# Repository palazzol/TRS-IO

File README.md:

# TRS-IO

TRS-IO gives a TRS-80 Model 1/III online capabilities and provides
access to a variety of services. TRS-IO currently features the
following capabilities:

1. Access to the <a href="https://retrostore.org">RetroStore</a>
2. <a href="http://frehd.com">FreHD</a> emulation
3. Access to files mounted on a SMB share or located on a micro-SD card
4. Access to remote servers via TCP
5. Virtual printer support

The TRS-IO versions for the Model 1 have some additional features that
are explained below. The following sections give an overview of TRS-IO as well as setup
instructions. This Github repository contains the complete source code
as well as the KiCad schematics for the PCB (Printed Circuit Board).
For the following descriptions it is assumed that an assembled TRS-IO
card is available.

### Overview

The figure below depicts the overall architecture. The TRS-80 machine
is connected to TRS-IO via the I/O Bus.  TRS-IO has a WiFi module that
connects to the local WiFi router. This allows TRS-IO to connect to
the Internet and access various services. Note that TRS-IO can only
connect to a 2.4 GHz WiFi network.

### Prerequisites

TRS-IO requires a TRS-80 Model III with 48kB of RAM or a Model 1 with 16kB of RAM.
Floppy disk drives or a cassette tape are not required.

### Feature list

TRS-IO support
TRS-IO comes in three different versions:

* TRS-IO for the Model III
* TRS-IO for the Model I using a builtin 32kB SRAM
* TRS-IO for the Model I using an FPGA

In the following, each of the versions is explained in detail.

### TRS-IO for the Model III

The following figure shows the top view of the TRS-IO card for the Model III:

1. Power supply via a micro-USB connector
2. Multi-color status LED
3. Status button
4. TRS-80 I/O bus connector
5. Micro-SD card reader
6. Disable FreHD jumper

The TRS-IO card needs to be connected to the TRS-80 Model III's I/O
Bus via a 50-pin ribbon cable (4). Furthermore, the TRS-IO card needs
a separate power supply via a standard 5V USB charger. The micro-USB
connector (1) plugs into the side of the TRS-IO card. The push button
(3) and the multi-color status LED (2) will be explained in the
configuration section.

### TRS-IO for the Model 1 (SRAM edition)

The following figure shows the top view of the TRS-IO card for the Model 1:

1. Power supply via a micro-USB connector
2. Multi-color status LED
3. Status button
4. TRS-80 I/O bus connector
5. Micro-SD card reader

The TRS-IO version for the Model 1 is almost identical to the Model III.
One difference is the I/O bus connector (4) is compatible with the 40-pin
expansion interface of the Model 1. There are several additional features
for the Model 1 version that are not relevant to the Model III version:

* A 32kB SRAM chip for a total of 48kB of total RAM.
* 25ms heartbeat timer to trigger the realtime clock.
* FreHD auto-boot for an unmodified M1.

### TRS-IO for the Model 1 (FPGA edition)

The TRS-IO project features a second version for the Model 1 that makes use
of an FGPA (Field Programmable Gate Array). Using an FPGA allows for some
advanced features not possible with the SRAM edition of TRS-IO. The following
figure shows the top view of the FPGA version for the Model 1:

1. Power supply via a micro-USB connector
2. Multi-color status LED
3. Status button
4. TRS-80 I/O bus connector
5. Micro-SD card reader
6. N/A
7. VGA connector
8. A15/VU configuration jumpers

This version of TRS-IO offers all the features of the SRAM edition of TRS-IO
as outlined in the previous section. Additionally, the FPGA edition also
offers a VGA connector (7) that can be used instead of a CRT monitor. This version
of TRS-IO also emlates the LE18 graphics cards. The color of the VGA signal can
be set to white (X=0), green (X=1), and amber (X=2) via the following OUT statements:

```OUT 31,0:OUT 31,5:OUT 31,X```

There are two configuation jumpers (8):
With the VU jumper, the ESP also powers the FPGA. When using this jumper, the FPGA
SHOULD NOT be powered via its own micro-USB connector; power should only be supplied
to the ESP's micro-USB connector (1). The A15 jumper regulates
the address range the FPGA responds to. Without the A15 jumper, the FPGA only
responds to memory read/write requests for the upper 32 kB (essentially mimicking the
upper RAM of the SRAM edition). With the A15 jumper, the FPGA will respond to the
complete 64kB address space of the Z80. This requires a modified Model 1 as the FPGA also
responds to ROM read requests.

### Configuring TRS-IO

The core of the TRS-IO card is an ESP32 microcontroller that features
a WiFi module that is used to connect to a WiFi router. After
physically connecting the TRS-IO card to a TRS-80 Model 1/III as
explained in the previous sections, the WiFi module on the ESP32
microcontroller first needs to be be configured with the credentials
of the local WiFi network.

While in setup mode, the TRS-IO's status LED will continuously blink
in white to indicate that it has not yet been configured. While in
that mode, TRS-IO will create an open access point called
"TRS-IO". Use a laptop to connect to this WiFi network and then use a
browser to visit URL <a
href="http://trs-io.local">trs-io.local</a>. The following web page
should appear in the browser:

Some hosts do not correctly handle mDNS that is used to resolve <a
href="http://trs-io.local">trs-io.local</a>. In that case, visit the
IP address <a href="http://192.168.4.1">192.168.4.1</a> instead.
The web interface shown above can be used to configure SSID and password of the WiFi
network that TRS-IO should connect to, the local timezone as well as
the credentials of a SMB share. For open networks leave the WiFi
password field empty. Note that TRS-IO cannot connect to WiFi networks
that use a capture portal. The timezone as well as the SMB share are
not required but will result in limited functionality.

Once all the information is provided, click on submit to upload the
parameters. TRS-IO will automatically reboot and try to connect to the
specified WiFi network. If successful, the LED will turn green for a
few seconds. If the credentials are wrong or if the specified WiFi
network is not accessible, the LED light will turn permanently red.

Note that TRS-IO will store all parameters in its local flash memory,
so the setup only needs to be performed once. Once TRS-IO is connected
to a WiFi router, it should still be possible to access URL <a
href="http://trs-io.local">trs-io.local</a> from a browser on the same
WiFi network. If mDNS is not supported by the host, the following BASIC
program can be used to determine TRS-IO's local IP address that was
assigned by the router:

```
10 OUT 236,16
20 OUT31,0:OUT31,4
30 C=INP(31):IF C=0 THEN END
40 PRINT CHR$(C);
50 GOTO 30
```

The web interface will also display two icons to indicate the status
of the SMB share and the micro-SD card (see screenshot above). Green
icons indicate that TRS-IO has access. Red icons indicate an error.
In that case, hovering the mouse over the red icon will display the
error message. It should be noted that TRS-IO needs to be rebooted
whenever a micro-SD card is inserted or ejected.

Pushing the status button will make the LED flash twice. The first time for
the WiFi status (green: WiFi connected; red: WiFi not connected) and a
second time for the SMB status (green: connected to SMB share; red:
not connected to SMB share). With proper configuration parameters, the
LED should flash green twice. Holding down the push button for more
than three seconds will erase all configuration parameters and place
TRS-IO back into setup mode (status LED flashing white). This
might be necessary if TRS-IO is moved to a different WiFi network.

The status LED indicates the state of TRS-IO:

* Blinking white: TRS-IO is not configured. It will create an open WiFi access point named "TRS-IO"
* Solid green: when TRS-IO has been configured with WiFi credentials and TRS-IO was able
  to connect to the WiFi network, the status LED will light in solid green for several seconds.
* Solid red: TRS-IO was configured with WiFi credentials but it was not possible to connect to the specified
  network. The reason could be wrong credentials or the specified network is itself offline. The push button can be
  used to reset TRS-IO into setup mode in case different credentials need to be provided.
* Solid blue: TRS-IO performs an OTA (Over-the-Air) update. TRS-IO will automatically detect
  newer firmware versions and will download and install the new firmware. The status LED will light solid blue during
  this process.
* Off: the status LED will be off during regular operations when TRS-IO is connected to the specified
  WiFi network and ready to accept commands from the TRS-80 Model III.
 
### FreHD

TRS-IO is compatible with the popular <a
href="http://frehd.com">FreHD</a> hard disk emulator. The FreHD disk
images can either be stored on a SMB share or on a micro-SD card.
If a micro-SD card is inserted, it will take precedence over
a mounted SMB share. Once TRS-IO is configured to access a SMB share,
simply copy the required files such as <a
href="http://members.iinet.net.au/~ianmav/trs80/downloads.htm">FREHD.ROM</a>
to the SMB share. Alternatively, the disk images can be transferred
to the micro-SD card. The IMPORT/EXPORT utilities will access files on the
SMB share or micro-SD card respectively.

### Virtual Printer Interface

TRS-IO support a virtual printer interface. Visiting <a
href="http://trs-io.local/printer">trs-io.local/printer</a> from a browser
will open the printer interface. Any printer output from the M1/MIII will
be displayed in the printer interface. If the host cannot resolve the mDNS name
trs-io.local, the above BASIC program can be used to determine the TRS-80's
IP address.

 ### Launching the native RetroStore Client

The <a href="https://retrostore.org">RetroStore</a> hosts applications
for the Tandy Radio Shack vintage computers and allows to seamlessly
download and run these applications without the need of cassettes or
floppy disks. TRS-IO acts as a gateway to the <a
href="https://retrostore.org">RetroStore</a>. This requires to run a
program on the TRS-80 that interfaces with TRS-IO. This program is
available as a regular <a
href="https://github.com/apuder/TRS-IO/blob/master/src/esp/components/retrostore/rsclient.cmd">CMD</a>
executable.  For TRS-80 machines with attached physical floppy disks,
this CMD executable can be copied to a floppy disk and launched the
usual way. For TRS-80 machines that have neither floppy disk drives
nor cassette drives, it is also possible to bootstrap the native
client via the following short BASIC program:
 
 ```BASIC
 10 OUT236,16
 20 OUT31,3
 30 OUT31,1
 40 N=INP(31)+256*INP(31)
 50 FOR X=1 TO N:POKE20735+X,INP(31):NEXT
 RUN
 SYSTEM
 *? /20736
 ```
 
The above BASIC program will download the CMD executable from TRS-IO
and launch the native client.  Note that this procedure needs to be
repeated every time the TRS-80 is turned on.
 
### Using the native RetroStore Client

After successfully launching the native RetroStore client, the monitor
of the TRS-80 should look like this:

The screenshot above shows the main menu of the native RetroStore
client. The arrow indicates the currently selected menu item.  The up
and down cursor keys can be used to move between the various menu
items. Hitting the ENTER key will activate the currently selected
menu item. Pressing CLEAR or BREAK in sub-menus will return to the
previous menu.
 
Keyboard controls:
 
 * Cursor up/down: toggle menu selection
 * ENTER: select current menu selection
 * BREAK/CLEAR: exit to previous screen

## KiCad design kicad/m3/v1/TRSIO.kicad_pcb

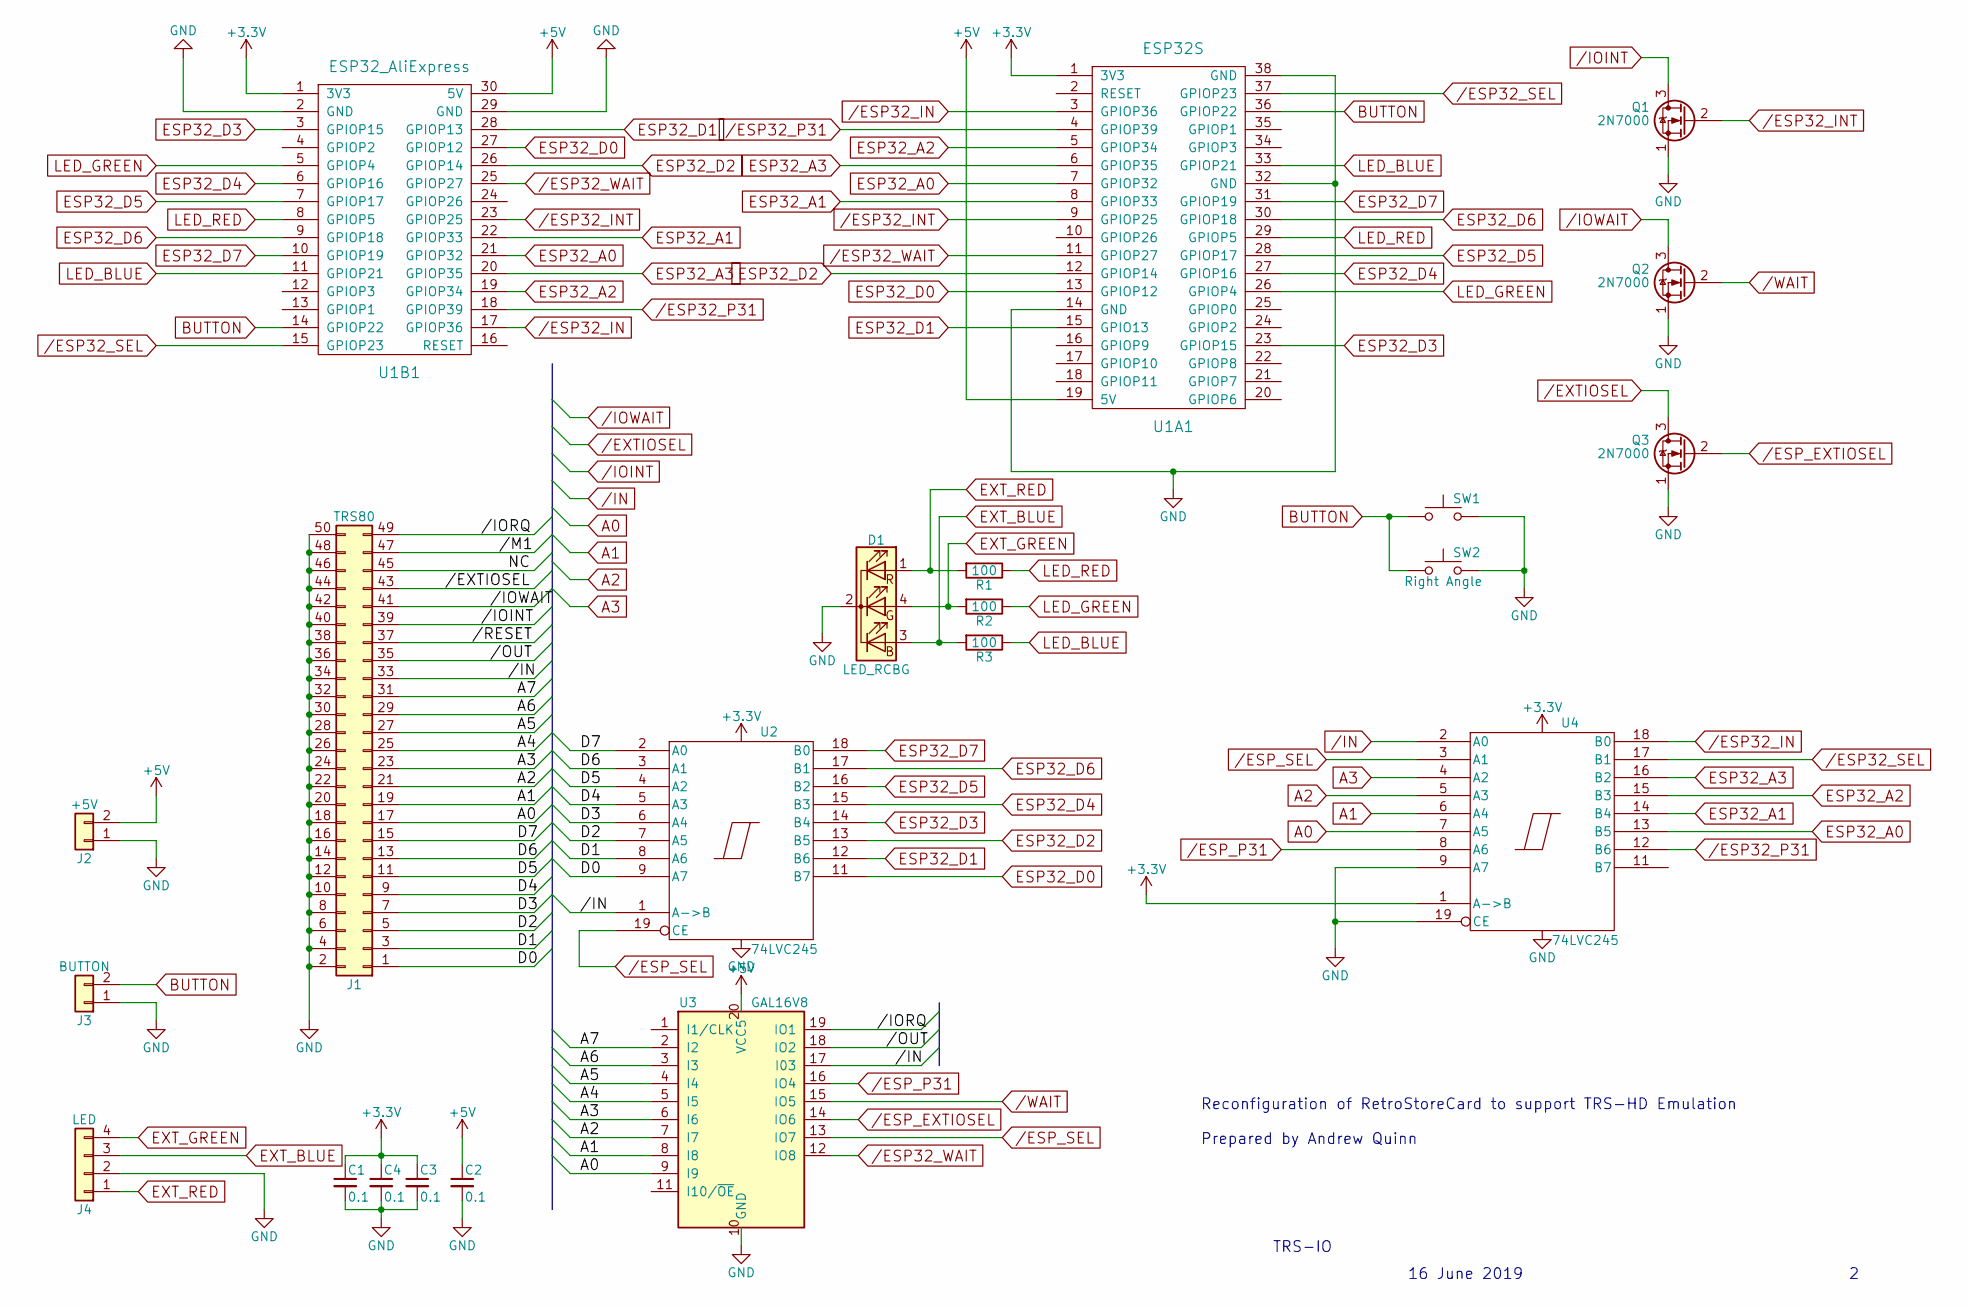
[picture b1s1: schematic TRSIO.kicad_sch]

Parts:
C1, C2, C3, C4: 0.1; C_Disc_D3.0mm_W2.0mm_P2.50mm
D1: LED_RCBG; LED_D5.0mm-4
J1: TRS80; Pin_Header_Straight_2x25_Pitch2.54mm
J2: +5V; Pin_Header_Straight_1x02_Pitch2.54mm
J3: BUTTON; Pin_Header_Straight_1x02_Pitch2.54mm
J4: LED; Pin_Header_Straight_1x04_Pitch2.54mm
Q1, Q2, Q3: 2N7000; TO-92_Molded_Narrow
R1, R2, R3: 100; R_Axial_DIN0207_L6.3mm_D2.5mm_P7.62mm_Horizontal
SW1: SW_Push; SW_PUSH_6mm_h9.5mm
SW2: Right Angle; SW_Tactile_SPST_Angled_PTS645Vx31-2LFS
U1A1: ESP32S; DIP-38_W22.9mm
U1B1: ESP32_AliExpress; DIP-30_W25.4mm
U2, U4: 74LVC245; DIP-20_W7.62mm
U3: GAL16V8; DIP-20_W7.62mm

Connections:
+3V3: C1.1, C3.1, C4.1, U1A1.1 (3V3), U1B1.1 (3V3), U2.20 (VCC), U4.1 (A->B), U4.20 (VCC)
+5V: C2.1, J2.2, U1A1.19 (5V), U1B1.30 (5V), U3.20 (VCC5)
//IORQ: J1.49, U3.19 (IO1)
//OUT: J1.35, U3.18 (IO2)
/A4: J1.25, U3.5 (I5)
/A5: J1.27, U3.4 (I4)
/A6: J1.29, U3.3 (I3)
/A7: J1.31, U3.2 (I2)
/D0: J1.1, U2.9 (A7)
/D1: J1.3, U2.8 (A6)
/D2: J1.5, U2.7 (A5)
/D3: J1.7, U2.6 (A4)
/D4: J1.9, U2.5 (A3)
/D5: J1.11, U2.4 (A2)
/D6: J1.13, U2.3 (A1)
/D7: J1.15, U2.2 (A0)
/ESP32_IN: U1A1.3 (GPIOP36), U1B1.17 (GPIOP36), U4.18 (B0)
/ESP32_INT: Q1.2 (G), U1A1.9 (GPIOP25), U1B1.23 (GPIOP25)
/ESP32_P31: U1A1.4 (GPIOP39), U1B1.18 (GPIOP39), U4.12 (B6)
/ESP32_SEL: U1A1.37 (GPIOP23), U1B1.15 (GPIOP23), U4.17 (B1)
/ESP32_WAIT: U1A1.11 (GPIOP27), U1B1.25 (GPIOP27), U3.12 (IO8)
/ESP_EXTIOSEL: Q3.2 (G), U3.14 (IO6)
/ESP_P31: U3.16 (IO4), U4.8 (A6)
/ESP_SEL: U2.19 (CE), U3.13 (IO7), U4.3 (A1)
/EXTIOSEL: J1.43, Q3.3 (D)
/IN: J1.33, U2.1 (A->B), U3.17 (I03), U4.2 (A0)
/IOINT: J1.39, Q1.3 (D)
/IOWAIT: J1.41, Q2.3 (D)
/WAIT: Q2.2 (G), U3.15 (IO5)
A0: J1.17, U3.9 (I9), U4.7 (A5)
A1: J1.19, U3.8 (I8), U4.6 (A4)
A2: J1.21, U3.7 (I7), U4.5 (A3)
A3: J1.23, U3.6 (I6), U4.4 (A2)
BUTTON: J3.2, SW1.1, SW2.1, U1A1.36 (GPIOP22), U1B1.14 (GPIOP22)
ESP32_A0: U1A1.7 (GPIOP32), U1B1.21 (GPIOP32), U4.13 (B5)
ESP32_A1: U1A1.8 (GPIOP33), U1B1.22 (GPIOP33), U4.14 (B4)
ESP32_A2: U1A1.5 (GPIOP34), U1B1.19 (GPIOP34), U4.15 (B3)
ESP32_A3: U1A1.6 (GPIOP35), U1B1.20 (GPIOP35), U4.16 (B2)
ESP32_D0: U1A1.13 (GPIOP12), U1B1.27 (GPIOP12), U2.11 (B7)
ESP32_D1: U1A1.15 (GPIO13), U1B1.28 (GPIOP13), U2.12 (B6)
ESP32_D2: U1A1.12 (GPIOP14), U1B1.26 (GPIOP14), U2.13 (B5)
ESP32_D3: U1A1.23 (GPIOP15), U1B1.3 (GPIOP15), U2.14 (B4)
ESP32_D4: U1A1.27 (GPIOP16), U1B1.6 (GPIOP16), U2.15 (B3)
ESP32_D5: U1A1.28 (GPIOP17), U1B1.7 (GPIOP17), U2.16 (B2)
ESP32_D6: U1A1.30 (GPIOP18), U1B1.9 (GPIOP18), U2.17 (B1)
ESP32_D7: U1A1.31 (GPIOP19), U1B1.10 (GPIOP19), U2.18 (B0)
EXT_BLUE: D1.3 (BA), J4.3, R3.2
EXT_GREEN: D1.4 (GA), J4.4, R2.2
EXT_RED: D1.1 (RA), J4.1, R1.2
GND: C1.2, C2.2, C3.2, C4.2, D1.2 (K), J1.2, J1.4, J1.6, J1.8, J1.10, J1.12, J1.14, J1.16, J1.18, J1.20, J1.22, J1.24, J1.26, J1.28, J1.30, J1.32, J1.34, J1.36, J1.38, J1.40, J1.42, J1.44, J1.46, J1.48, J1.50, J2.1, J3.1, J4.2, Q1.1 (S), Q2.1 (S), Q3.1 (S), SW1.2, SW2.2, U1A1.14 (GND), U1A1.32 (GND), U1A1.38 (GND), U1B1.2 (GND), U1B1.29 (GND), U2.10 (GND), U3.10 (GND), U4.9 (A7), U4.10 (GND), U4.19 (CE)
LED_BLUE: R3.1, U1A1.33 (GPIOP21), U1B1.11 (GPIOP21)
LED_GREEN: R2.1, U1A1.26 (GPIOP4), U1B1.5 (GPIOP4)
LED_RED: R1.1, U1A1.29 (GPIOP5), U1B1.8 (GPIOP5)

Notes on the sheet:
TRS-IO
16 June 2019
Reconfiguration of RetroStoreCard to support TRS-HD Emulation Prepared by Andrew Quinn

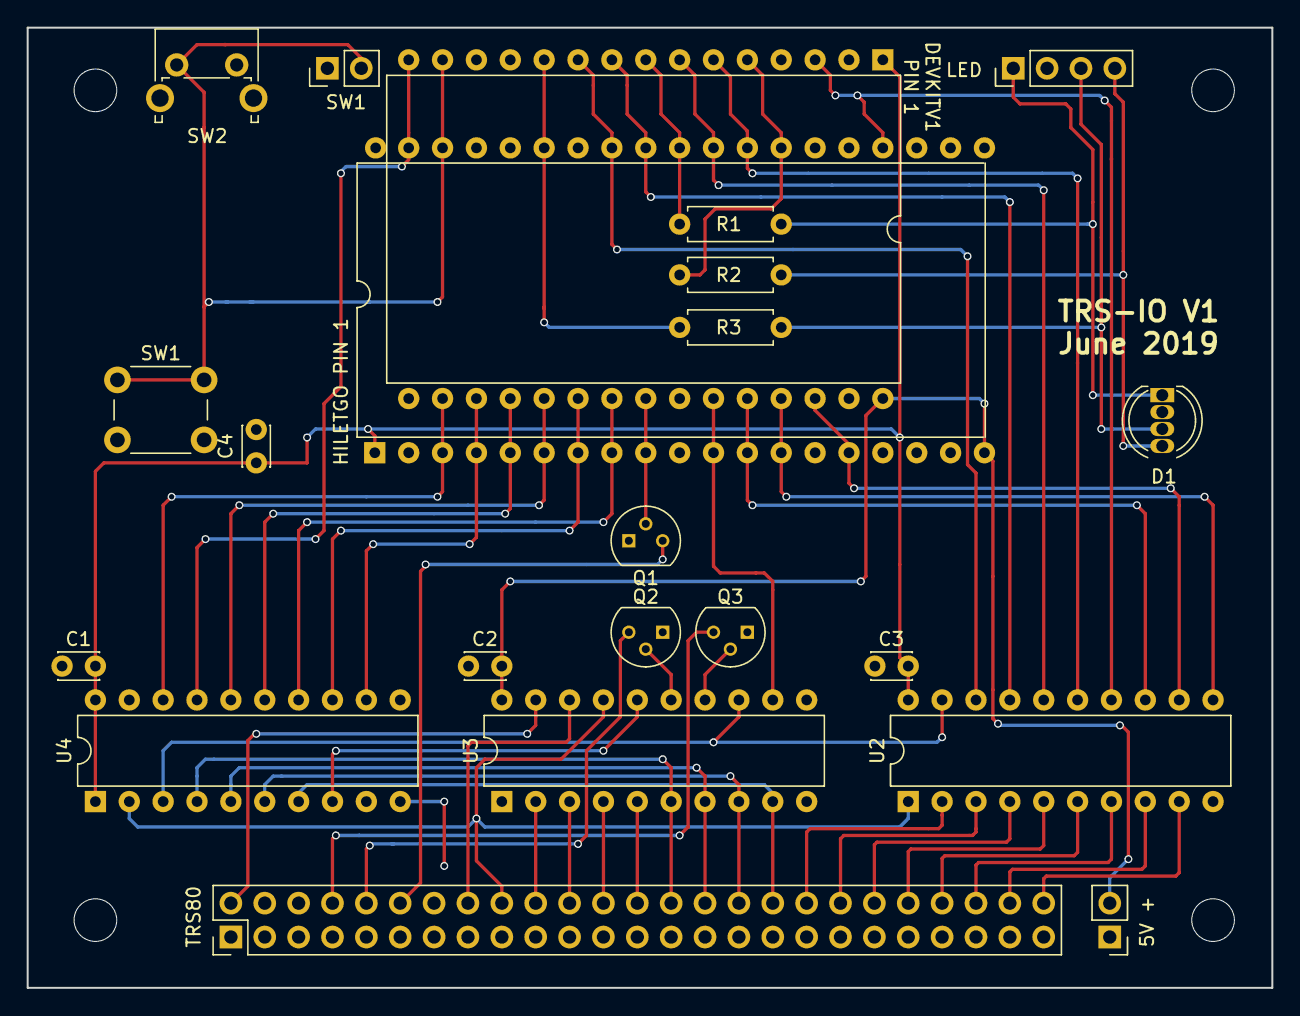
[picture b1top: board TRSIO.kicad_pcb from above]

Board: 2 copper layers, 93.3 x 72.0 mm, 22 parts (0 on the bottom side), 53 nets.

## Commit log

2022-05-10 Migrate RSC to TRS-LIB
2022-05-19 Update libsmb2
2022-05-19 Reduce SPI speed due to use of GPIO matrix
2022-10-02 Convert m3 v1 to KiCAD 6.0, add .gitignore for all KiCAD
